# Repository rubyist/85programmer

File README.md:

# 85Programmer

This is a simple arduino shield for using an arduino to quickly program attiny85
microprocessors.

You can do this with an arduino and a breadboard, or you can buy a pre-made USB
programmer. I happened to have everything on hand to build one and I got tired
of using and wiring up a breadboard to do this, so I built this shield.

## Building

Use whatever method you prefer for building the pcb. Along with the Eagle files
I've included a PDF you can print for the toner transfer and photo-resist methods.

You'll need:

* Some pcb and a method to etch or mill it
* 10uF capacitor
* 8 pin dip socket
* pin headers suitable for an arduino shield

## Programming

For this, I assume working with the Arduino IDE. Anything else and you're on
your own.

1. Load the ArduinoISP sketch (File -> Examples) onto your arduino.
2. Set the board to be ATtiny85 (internal 8MHz clock).
3. Set the programmer to be Arduino as ISP
4. Put the shield on the arduino, stick an ATtiny85 into the socket
5. If it's the first time you've programmed the chip, run Burn Bootloader
6. Write your arduino code and upload it as normal.
7. Use your newly programmed ATtiny85!

## License

This work is licensed under a Creative Commons Attribution-NonCommercial-ShareAlike 4.0 International License.

http://creativecommons.org/licenses/by-nc-sa/4.0/deed.en_US

## Contributing

Got feedback or fixes? Fork and PR me!

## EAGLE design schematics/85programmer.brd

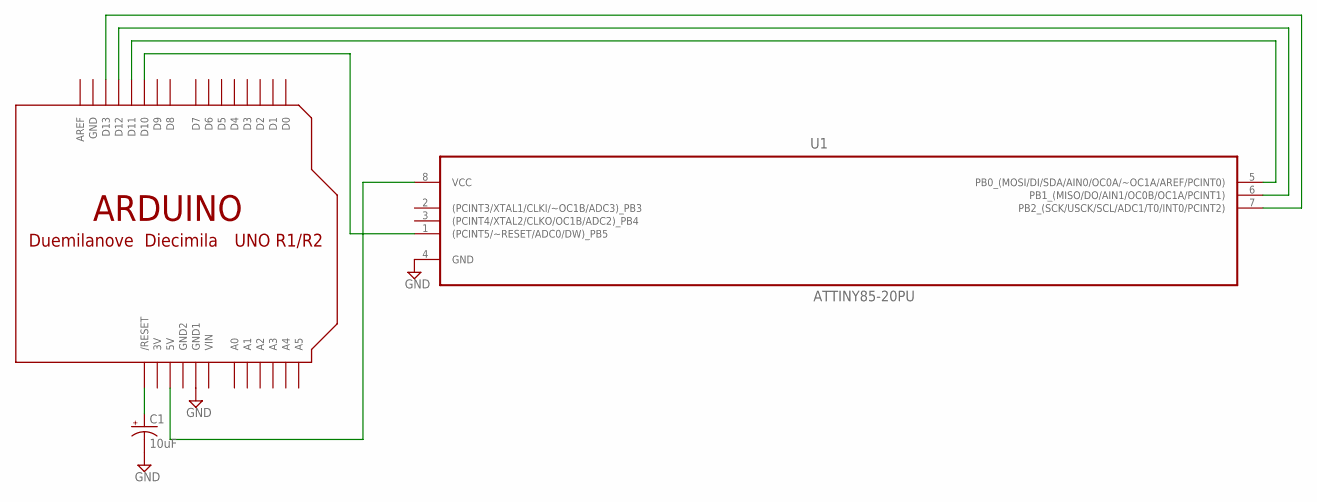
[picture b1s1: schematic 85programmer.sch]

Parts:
C1: 10uF; E2,5-6E
U1: ATTINY85-20PU; DIP254P762X533-8
U$1: ARDUINOUNO; ARDUINO

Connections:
3V: U$1.3V
GND: C1.-, U1.4 (GND), U$1.GND, U$1.GND1
GND2: U$1.GND2
unnamed: C1.+, U$1.RESET (/RESET)
unnamed: U1.8 (VCC), U$1.5V
unnamed: U1.5 (PB0_(MOSI/DI/SDA/AIN0/OC0A/~OC1A/AREF/P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), U$1.D11
unnamed: U1.6 (PB1_(MISO/DO/AIN1/OC0B/OC1A/PCINT1)), U$1.D12
unnamed: U1.7 (PB2_(SCK/USCK/SCL/ADC1/T0/INT0/PCINT2)), U$1.D13
unnamed: U1.1 ((PCINT5/~RESET/ADC0/DW)_PB5), U$1.D10
VIN: U$1.VIN

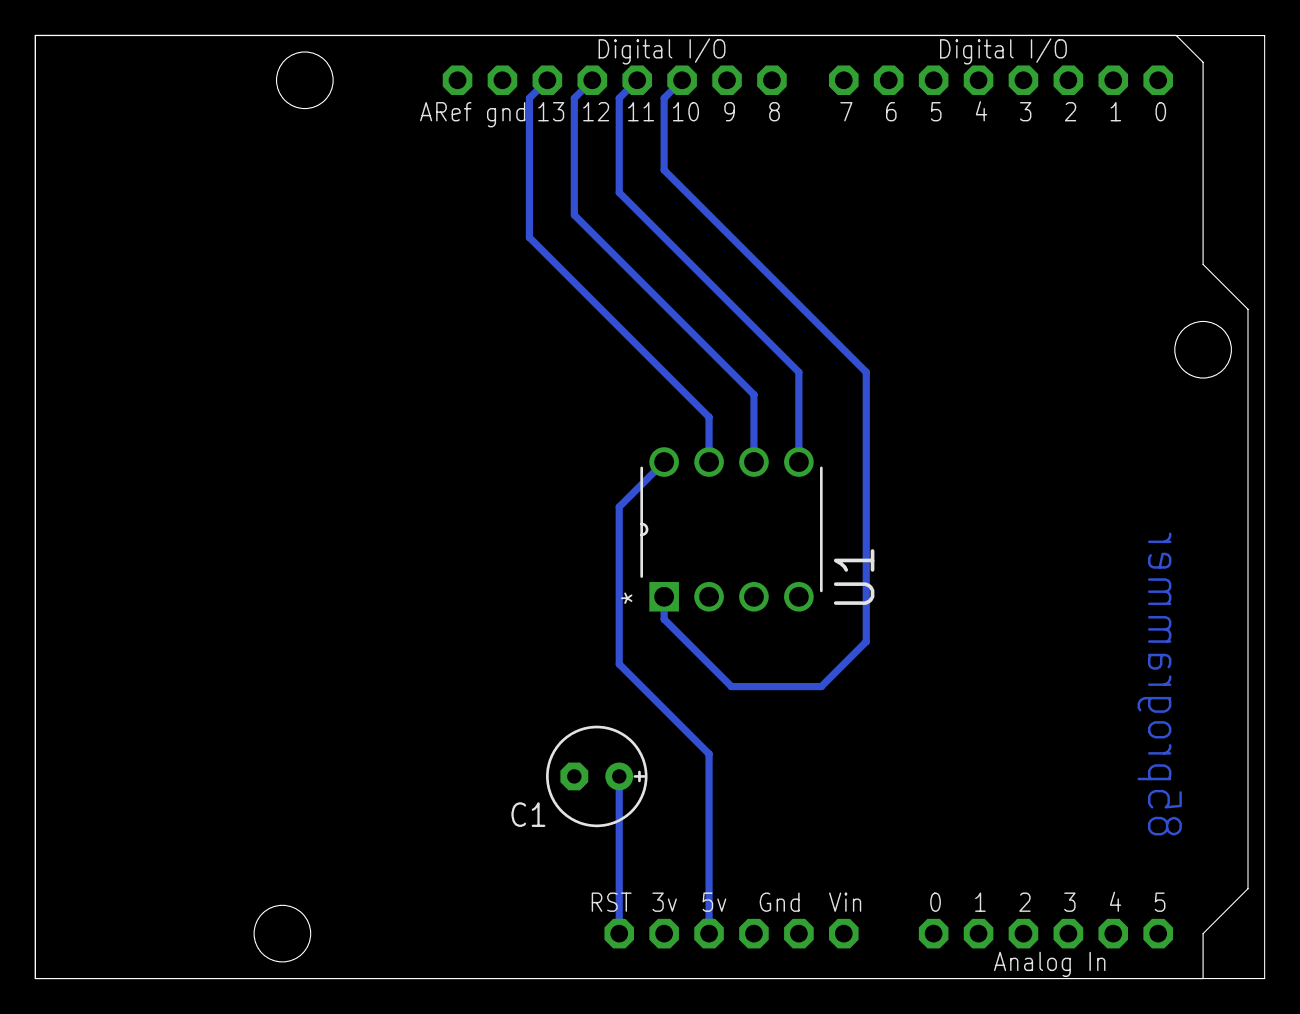
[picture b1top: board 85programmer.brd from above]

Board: 2 copper layers, 69.5 x 53.3 mm, 3 parts (0 on the bottom side), 7 nets.

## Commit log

2014-02-25 readme
2014-02-26 schematics and board layout
2014-02-26 Add pdf of pcb layout
2014-02-26 Update readme with instructions
2014-02-26 Add capacitor value to schematics
